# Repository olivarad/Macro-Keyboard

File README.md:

# Macro-Keyboard

Welcome to the Macro Keyboard project repository! This project focuses on designing a customizable macro keyboard. Please follow the instructions below to explore the KiCad files and project details.

## Getting Started

To view the KiCad files, ensure you have KiCad and the necessary project dependencies installed on your system. The required dependencies can be found in the "Dependencies" folder within this repository.

## Quick Board Preview

If you prefer a quicker way to view the board without installing additional dependencies, you can use a Gerber file viewer. Simply navigate to the "Gerber" folder in this repository and use a compatible viewer to inspect the board layout.

## Viewing with KiCad

For a comprehensive view of the project and detailed editing capabilities, follow these steps:

1. Install [KiCad](https://www.kicad.org/download/).
2. Install the project dependencies from the "Dependencies" folder.

## Exploring the Project

The project is organized into folders:

- **Gerber**: Includes Gerber files for quick board preview.
- **KiCad**: Holds the KiCad project files.

## Contributing

Feel free to contribute to the project by forking the repository, making your changes, and submitting a pull request. We welcome any improvements, bug fixes, or new features!

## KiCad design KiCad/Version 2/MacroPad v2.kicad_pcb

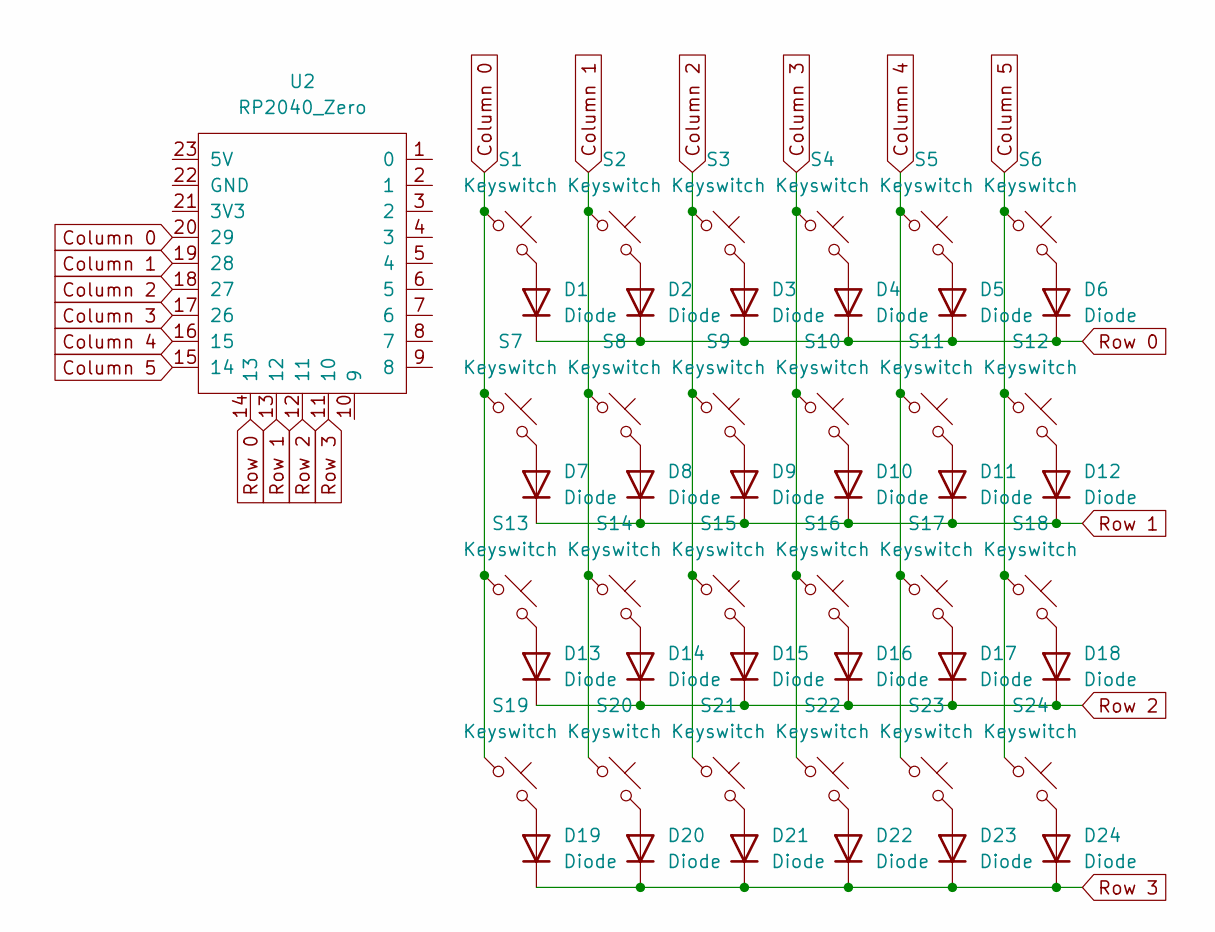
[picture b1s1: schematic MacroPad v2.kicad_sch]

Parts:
D1, D2, D3, D4, D5, D6, D7, D8, D9, D10, D11, D12, D13, D14, D15, D16, D17, D18, D19, D20, D21, D22, D23, D24: Diode; Diode_SOD-123
S1, S2, S3, S4, S5, S6, S7, S8, S9, S10, S11, S12, S13, S14, S15, S16, S17, S18, S19, S20, S21, S22, S23, S24: Keyswitch; SW_Hotswap_Kailh_Choc_V1V2
U2: RP2040_Zero; (effects (font (size 1.27 1.27)) (justify right))

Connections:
Column 0: S1.1, S7.1, S13.1, S19.1, U2.20 (29)
Column 1: S2.1, S8.1, S14.1, S20.1, U2.19 (28)
Column 2: S3.1, S9.1, S15.1, S21.1, U2.18 (27)
Column 3: S4.1, S10.1, S16.1, S22.1, U2.17 (26)
Column 4: S5.1, S11.1, S17.1, S23.1, U2.16 (15)
Column 5: S6.1, S12.1, S18.1, S24.1, U2.15 (14)
unnamed: D1.2 (A), S1.2
unnamed: D2.2 (A), S2.2
unnamed: D3.2 (A), S3.2
unnamed: D4.2 (A), S4.2
unnamed: D5.2 (A), S5.2
unnamed: D6.2 (A), S6.2
unnamed: D7.2 (A), S7.2
unnamed: D8.2 (A), S8.2
unnamed: D9.2 (A), S9.2
unnamed: D10.2 (A), S10.2
unnamed: D11.2 (A), S11.2
unnamed: D12.2 (A), S12.2
unnamed: D13.2 (A), S13.2
unnamed: D14.2 (A), S14.2
unnamed: D15.2 (A), S15.2
unnamed: D16.2 (A), S16.2
unnamed: D17.2 (A), S17.2
unnamed: D18.2 (A), S18.2
unnamed: D19.2 (A), S19.2
unnamed: D20.2 (A), S20.2
unnamed: D21.2 (A), S21.2
unnamed: D22.2 (A), S22.2
unnamed: D23.2 (A), S23.2
unnamed: D24.2 (A), S24.2
Row 0: D1.1 (K), D2.1 (K), D3.1 (K), D4.1 (K), D5.1 (K), D6.1 (K), U2.14 (13)
Row 1: D7.1 (K), D8.1 (K), D9.1 (K), D10.1 (K), D11.1 (K), D12.1 (K), U2.13 (12)
Row 2: D13.1 (K), D14.1 (K), D15.1 (K), D16.1 (K), D17.1 (K), D18.1 (K), U2.12 (11)
Row 3: D19.1 (K), D20.1 (K), D21.1 (K), D22.1 (K), D23.1 (K), D24.1 (K), U2.11 (10)

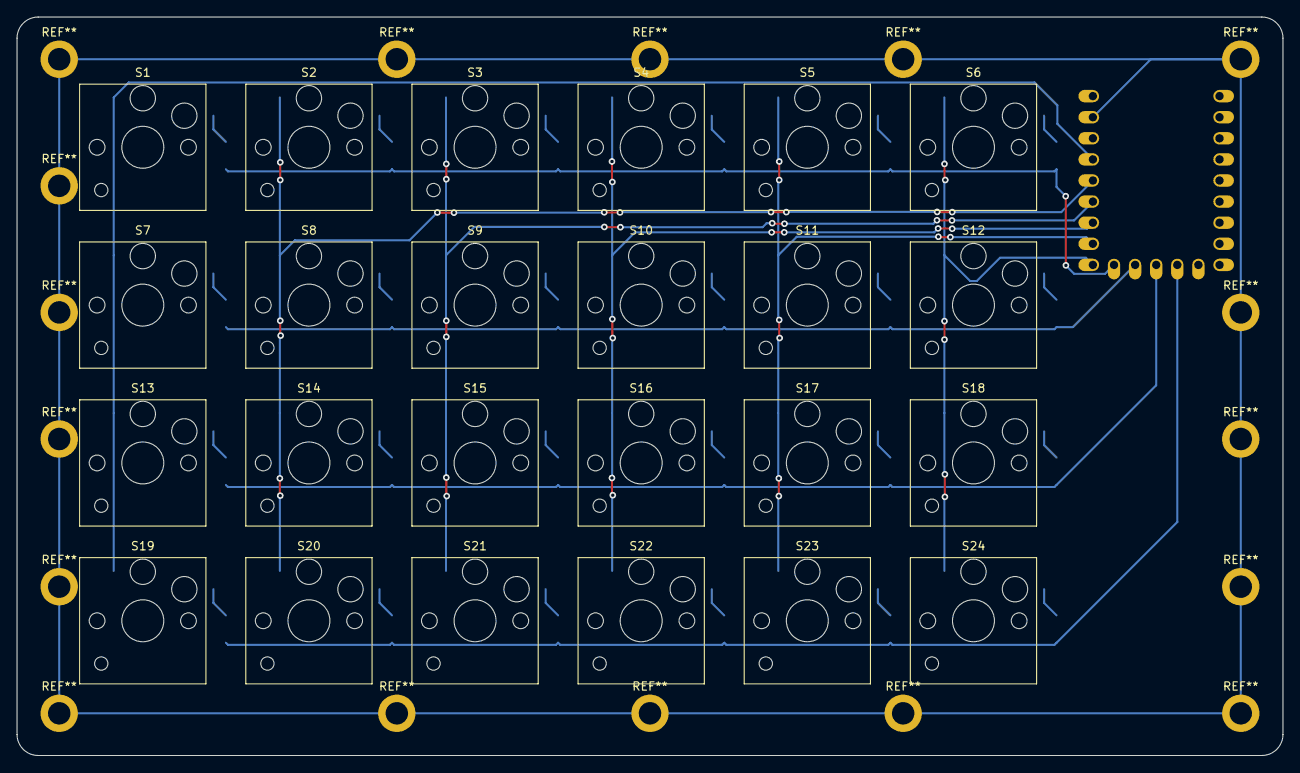
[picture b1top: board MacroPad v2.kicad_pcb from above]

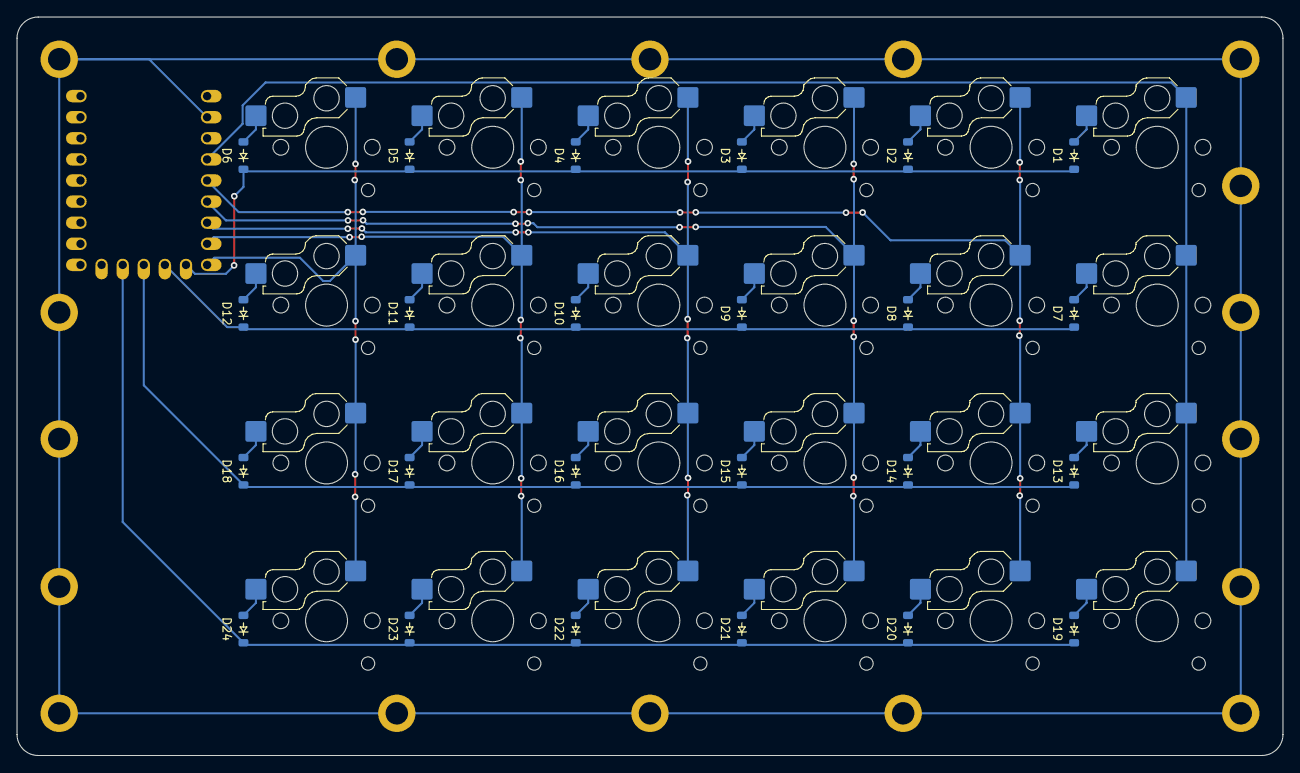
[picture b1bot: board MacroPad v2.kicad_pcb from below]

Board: 2 copper layers, 152.4 x 88.9 mm, 49 parts (24 on the bottom side), 34 nets.
